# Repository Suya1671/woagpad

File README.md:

# The Woagpad

## A macropad of all time

The woagpad is a board I decided to create because a macropad
kinda just sounds fun. I really also wanted the rotary encoders
to be able to change volume and control media playback (although RMK doesn't support it yet. Eventually:tm:).

## Features

- **Rust based firmware**: Through the power of [RMK](https://haobogu.github.io/rmk), the firmware is written in 100% Rust. Crab gaming :crab:
  - [VIAL](https://get.vial.today/) support OOTB
- **128x32 OLED Display**: Display whatever the hell you want*
- **2 EC11 Rotary Encoders**: Control your volume or scroll through pages with these*
- **3x3 key matrix**: Keypad, macro, media controls, whatever the hell you want. You have 9 keys to mess around with (this includes the push buttons on the rotary encoders)

*The default rmk firmware does not support OLED display or rotary encoders yet.
Once those are implemented, the firmware will be updated to support them.
Write your own firmware to take advantage of these features!

## Design

### PCB

Bog standard PCB Schematic for a macropad.
This is actually my first design that uses a matrix
and an OLED display so that's fun.

Also yes, 2 encoders can share a pin! Neat.

|Front|Back|
|---|---|
|||

First PCB with actual mounting holes.
although in this case, the mounting holes are used
for mounting the top and bottom of the case.
See the case design for more details.

### Case

Top integrated plate + frame. Bottom half with standoffs
for heat inserts to screw the two halves together.

Also yes, the encoder holes are slightly larger than the encoders.
I have no idea how well they'll actually fit so I decided for
more tolerance than normal. It'll be fine... right?

### BOM
- 1x PCB
  - see production/gerber.zip
- 1x Case
  - see production/Top.step
  - see production/Bottom.step
- 7X Cherry MX Switches
- 7X DSA Keycaps
- 2X Rotary Encoders
- 9X 1N4148 Diodes
- 3X M3x5mx4mm Heatset inserts
- 3X M3x16mm Bolts
- 1x XIAO RP2040
- 1x 0.91" 128x64 OLED Display

## Extras
First time using [RMK](https://haobogu.github.io/rmk) for firmware. It was WAY easier compared to other firmware options.
Highly reccomend if you don't need additional features.

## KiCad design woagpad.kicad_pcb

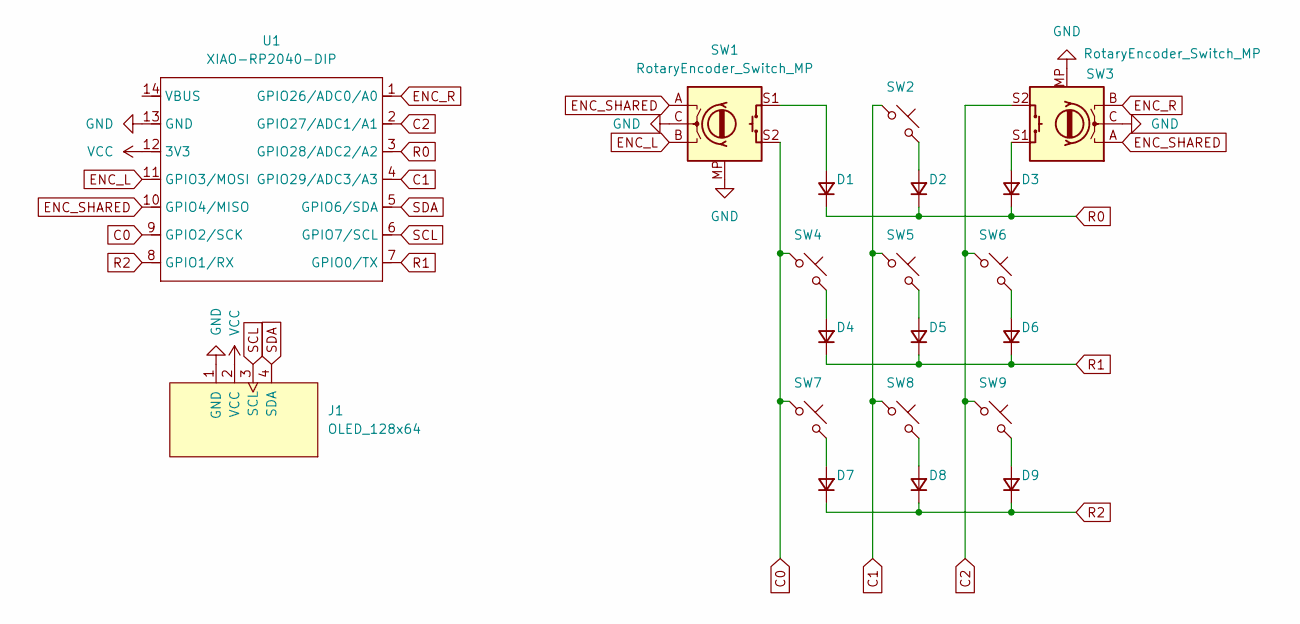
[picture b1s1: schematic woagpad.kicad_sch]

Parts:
D1, D2, D3, D4, D5, D6, D7, D8, D9: D; Diode_DO-35
J1: OLED_128x64; MODULE_DM-OLED096-636
SW1, SW3: RotaryEncoder_Switch_MP; Encoder_EC11_MX
SW2, SW4, SW5, SW6, SW7, SW8, SW9: SW_Push; MX_PCB
U1: XIAO-RP2040-DIP; Seeed_XIAO_RP2040

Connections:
C0: SW1.S2, SW4.1, SW7.1, U1.9 (GPIO2/SCK)
C1: SW2.1, SW5.1, SW8.1, U1.4 (GPIO29/ADC3/A3)
C2: SW3.S2, SW6.1, SW9.1, U1.2 (GPIO27/ADC1/A1)
ENC_L: SW1.B, U1.11 (GPIO3/MOSI)
ENC_R: SW3.B, U1.1 (GPIO26/ADC0/A0)
ENC_SHARED: SW1.A, SW3.A, U1.10 (GPIO4/MISO)
GND: J1.1 (GND), SW1.C, SW1.MP, SW3.C, SW3.MP, U1.13 (GND)
unnamed: D1.2 (A), SW1.S1
unnamed: D2.2 (A), SW2.2
unnamed: D3.2 (A), SW3.S1
unnamed: D4.2 (A), SW4.2
unnamed: D5.2 (A), SW5.2
unnamed: D6.2 (A), SW6.2
unnamed: D7.2 (A), SW7.2
unnamed: D8.2 (A), SW8.2
unnamed: D9.2 (A), SW9.2
R0: D1.1 (K), D2.1 (K), D3.1 (K), U1.3 (GPIO28/ADC2/A2)
R1: D4.1 (K), D5.1 (K), D6.1 (K), U1.7 (GPIO0/TX)
R2: D7.1 (K), D8.1 (K), D9.1 (K), U1.8 (GPIO1/RX)
SCL: J1.3 (SCL), U1.6 (GPIO7/SCL)
SDA: J1.4 (SDA), U1.5 (GPIO6/SDA)
VCC: J1.2 (VCC), U1.12 (3V3)

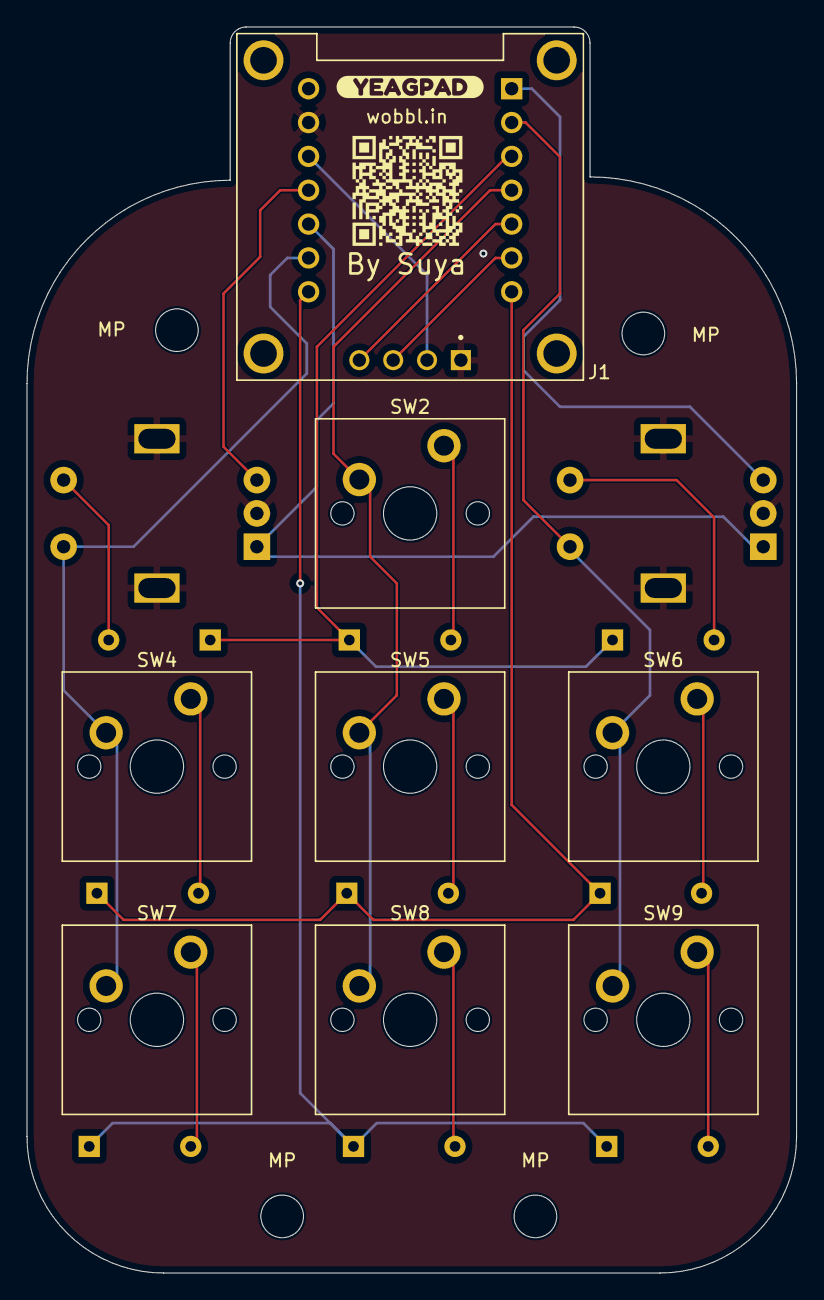
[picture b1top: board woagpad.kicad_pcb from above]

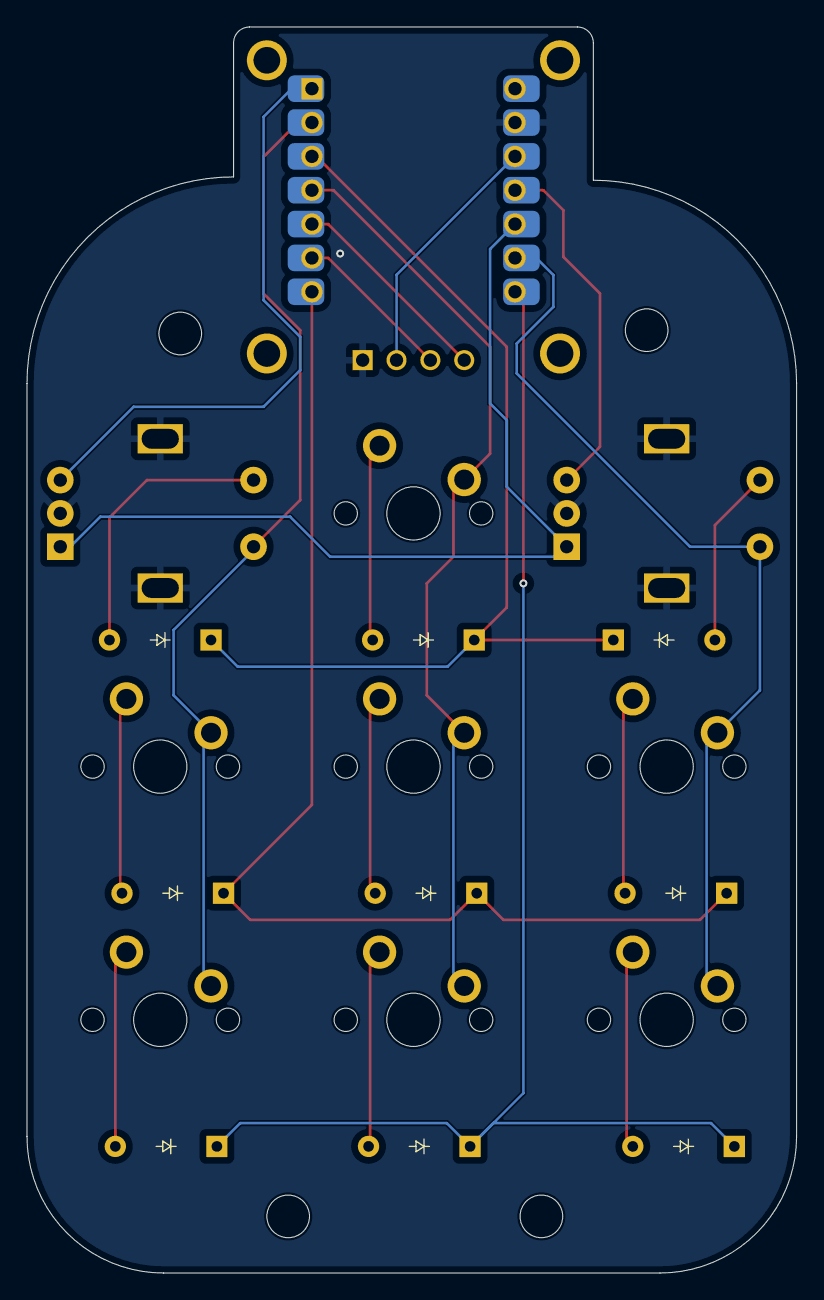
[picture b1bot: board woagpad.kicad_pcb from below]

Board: 2 copper layers, 57.8 x 93.5 mm, 26 parts (10 on the bottom side), 22 nets.

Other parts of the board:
MP: MountingHole_3.2mm_M3
MP#2, MP#3, MP#4: MountingHole_3.2mm_M3
QR*****: WobblQR
kibuzzard-67AA371A: G***; kibuzzard-67AA371A

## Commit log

2025-02-01 feat: initial commit
2025-02-02 feat: finish schematic
2025-02-13 feat: woagpad V0.1 PCB done
2025-02-18 feat: case and firmware
2025-02-18 wip: work on production files for hackpad submission
2025-02-19 feat: first submission draft
2025-02-19 feat: add motivation to readme
2025-02-19 chore: fix typo in readme
